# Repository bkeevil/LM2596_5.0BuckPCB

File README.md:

# LM2596_5.0BuckPCB

This EagleCAD PCB design is for a buck switched mode power supply.  

It is based on the example circuit in the LM2596S datasheet.  

http://www.ti.com/lit/ds/symlink/lm2596.pdf

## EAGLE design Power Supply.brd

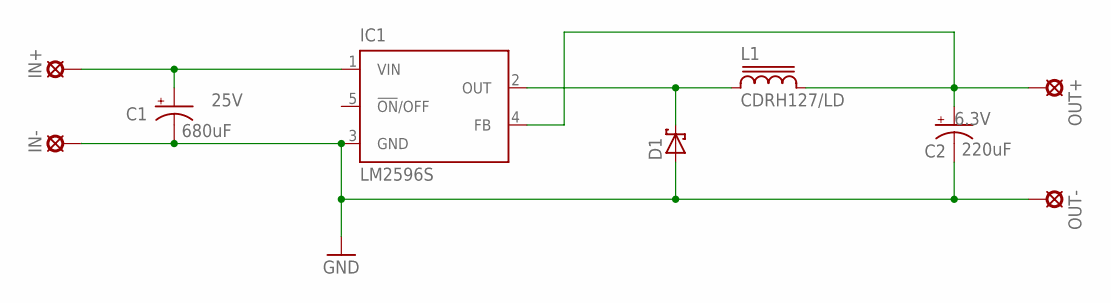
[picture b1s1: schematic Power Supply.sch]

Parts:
C1: 680uF; E5-10,5; VOLTAGE 25V
C2: 220uF; UD-6,3X5,8_NICHICON; VOLTAGE 6.3V
D1: SCHOTTKY-DIODESMD; SMB
IC1: LM2596S; TO263-5
IN+: LSP13
IN-: LSP13
L1: CDRH127/LD
OUT+: LSP13
OUT-: LSP13

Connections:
FB: C2.+, IC1.4 (FB), L1.2, OUT+.MP
GND: C1.-, C2.-, D1.A, IC1.3 (GND), IN-.MP, OUT-.MP
OUT: D1.C, IC1.2 (OUT), L1.1
VIN: C1.+, IC1.1 (VIN), IN+.MP

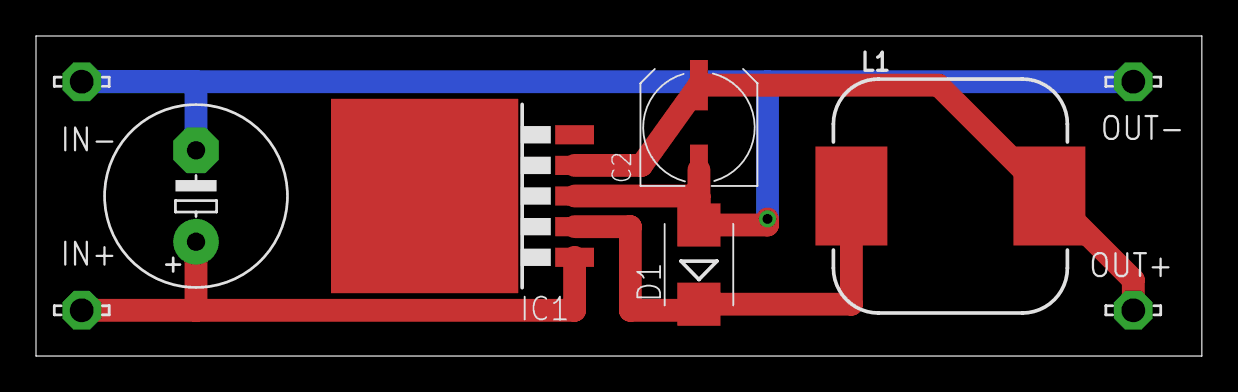
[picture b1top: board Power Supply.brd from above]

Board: 2 copper layers, 64.8 x 17.8 mm, 9 parts (0 on the bottom side), 4 nets.

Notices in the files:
parts and their libraries:
inductor-sumida: Copyright (C) 2008, Bob Starr
